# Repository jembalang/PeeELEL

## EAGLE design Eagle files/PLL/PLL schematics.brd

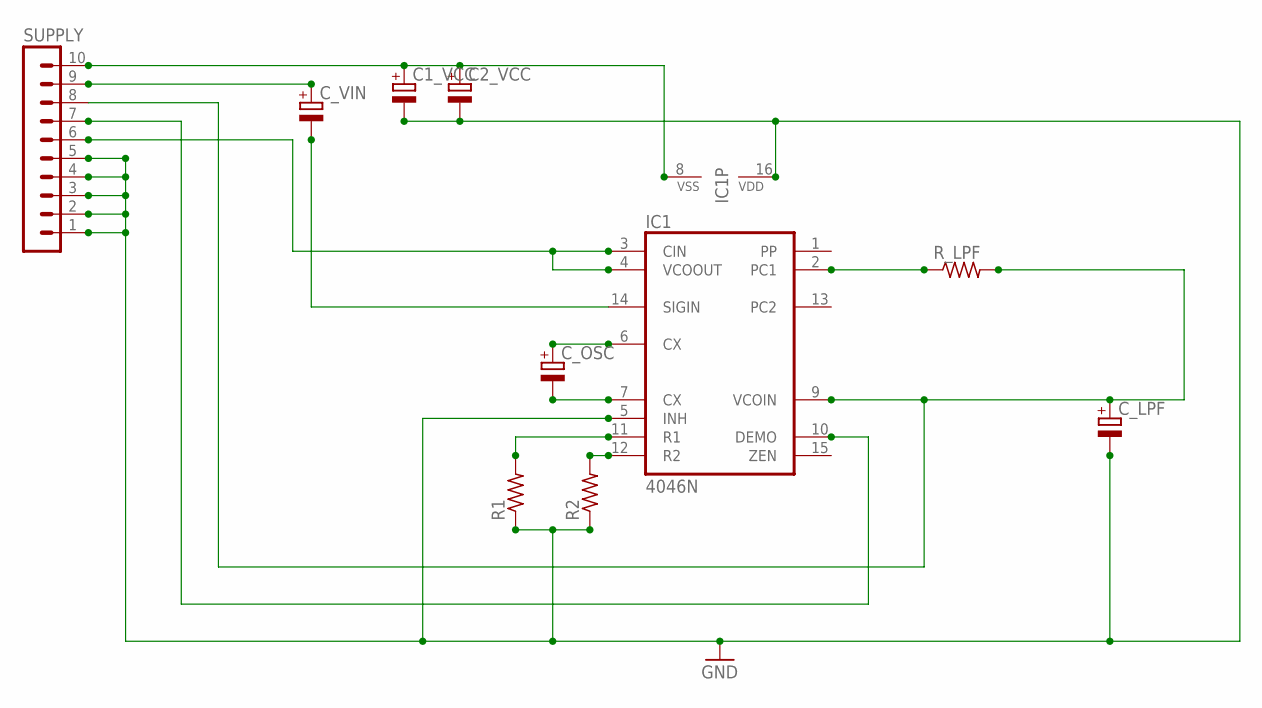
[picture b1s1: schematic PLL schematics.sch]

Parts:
C1_VCC, C2_VCC: CPOL-EUTAP5-50; TAP5-50
C_LPF: CPOL-EUTAP5-50; TAP5-50
C_OSC: CPOL-EUTAP5-50; TAP5-50
C_VIN: CPOL-EUTAP5-50; TAP5-50
IC1: 4046N; DIL16
R1, R2: R-US_0207/12; 0207/12
R_LPF: R-US_0207/12; 0207/12
SUPPLY: MA10-1

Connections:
GND: C1_VCC.-, C2_VCC.-, C_LPF.-, IC1.5 (INH), IC1.16 (VDD), R1.1, R2.1, SUPPLY.1, SUPPLY.2, SUPPLY.3, SUPPLY.4, SUPPLY.5
unnamed: C_OSC.+, IC1.6 (CX)
unnamed: C_OSC.-, IC1.7 (CX)
unnamed: C1_VCC.+, C2_VCC.+, IC1.8 (VSS), SUPPLY.10
unnamed: C_VIN.+, SUPPLY.9
unnamed: C_VIN.-, IC1.14 (SIGIN)
unnamed: IC1.3 (CIN), IC1.4 (VCOOUT), SUPPLY.6
unnamed: IC1.12 (R2), R2.2
unnamed: IC1.11 (R1), R1.2
unnamed: IC1.2 (PC1), R_LPF.1
unnamed: IC1.10 (DEMO), SUPPLY.7
unnamed: C_LPF.+, IC1.9 (VCOIN), R_LPF.2, SUPPLY.8

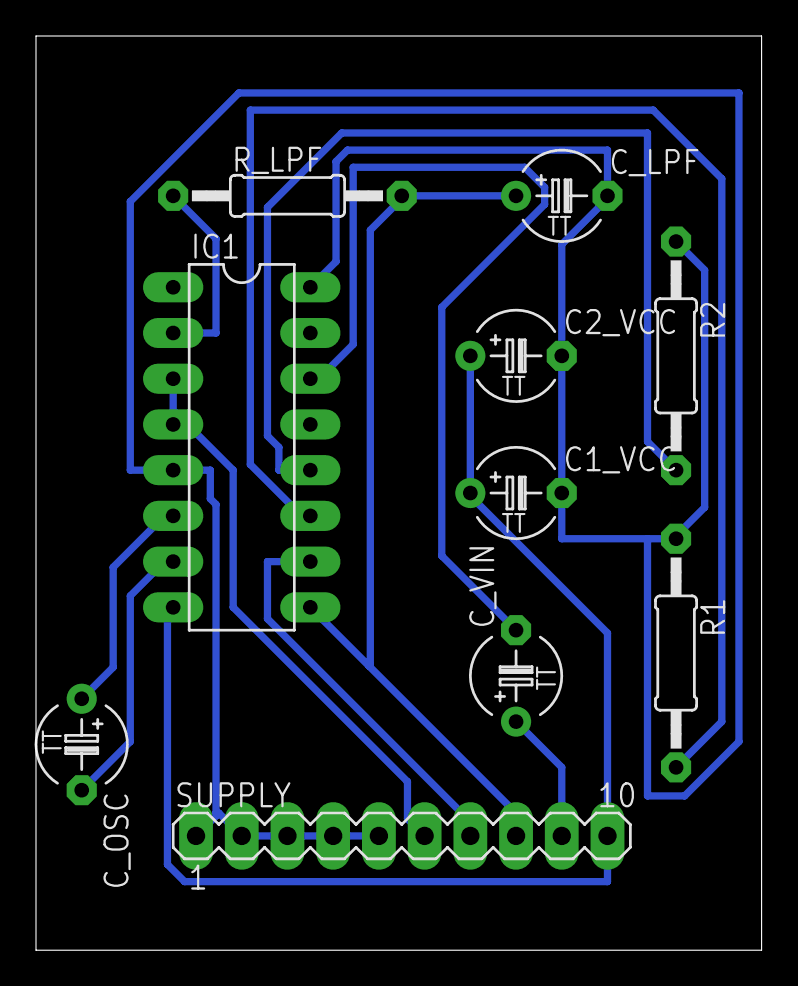
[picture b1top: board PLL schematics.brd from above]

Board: 2 copper layers, 40.3 x 50.8 mm, 10 parts (0 on the bottom side), 12 nets.

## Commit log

2016-07-24 Added design, schematics and PCB
    All files need to be opened using EAGLE.
